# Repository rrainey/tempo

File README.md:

# Tempo

## One Project, Three Boards

This repository is a collection point for a number of jump logging devices I designed for skydivers.

Three boards are part of the Tempo project: Tempo-BT, Tempo, and Peakick. All three explore modern sensor ICs for use in skydiving.  The Peakick board is more research oriented. 
Peakick is design as a daughter board for experimentation with a range of microcontroller boards. It is most easily connected to SparkFun "Thing Plus" form factor boards, although 
it can be connected to almost any modern MCU/SOC board designed for 3.3V peripherals.

Tempo is a purpose built single board logger derived from Peakick.  Essentially, it is a SAMD51 MCU dropped onto a Peakick board.  This project includes PlatformIO-based firmware to drive this board as a stand-alone
skydiving data logger.  The firmware is operational and reliable and I use this board most often for my logging experiments.

### Tempo-BT: Experiments in audible feedback for skydivers.

This project was originally designed to experiment with real-time audible feedback at assist a skydiver in freefall. The original Peakick design stacks a [SparkFun ESP32 Thing Plus](https://github.com/sparkfun/STM32_Thing_Plus) atop a custom GNSS/sensor combo board. The SparkFun board supports an audio connection to Bluetooth earbuds or headphones.  That work led me to design the Tempo-BT board.

### Sensors and Capabilities

- GPS/GNSS using a u-blox SAM-M10Q
- 6-DOF Inertial measurement / gyro using a ICM-42688-V
- Barometric pressure / temperature using a BPM390
- 3-DOF Compass/Magnetic measurement using a MMC5983MA

I am just getting started with this project, so all I'm doing for now is validating the sensor board designs and (soon) experimenting with basic BT audio capabilities.

## Directory Structure

| Folder      | Description |
| ----------- | ----------- |
| hardware    | KiCad PCB projects (using KiCad 7)    |
| hardware/peakick | (original) u-blox GNSS + IMU + Barometric sensor PCB |
| hardware/tempo |(newer design)  SAMD51 + u-blox GNSS + IMU + Barometric sensor PCB |
| hardware/tempo-bt |(newest design) u-blox NORA-B106 Bluetooth SOC (Nordic nRF5340) + u-blox GNSS + IMU + Barometric sensor PCB |
| enclosure    | 3D-printable enclosures (Fusion360 format)
| firmware    | various Arduino sketches (mostly for historical reference)       |
| platformio  | Platformio test and operational projects for the Tempo board |
| platformio/tempo-logger  | Skydiving logger firmware for the Tempo board - tested and reliable |

## Enclosure

The enclosures are designed to be SLA printable. I print using a MakerBot Replicator 2 with Cura 5.3.1 as the slicer. Print resolution set to 0.15mm.

The PCBs are secured to the enclosure using M2.5 brass inserts and screws. The inserts are heat-inserted into the bottom shell using a soldering iron after printing.

### PCB Notes

All three boards were created using KiCad.  In Peakick, in order to get the header alignment with the parent board as accurate as possible, I imported the [SparkFun STM32 Thing Plus](https://github.com/sparkfun/STM32_Thing_Plus) GitHub project to use its PCB layout. 

I prefer 1 oz. Copper with ENIG finish. I ordered the Peakick V1 PCB from OSHPark and stencils from OSH as well.  Tempo boards were ordered from PCBWay.

## Peakick Assembly Parts List

| QTY | MPN      | Description |
|----| ----------- | ----------- |
| 1 | [WRL-15663](https://www.digikey.com/en/products/detail/sparkfun-electronics/WRL-15663/11506265)   | SparkFun ESP32 Thing Plus WROOM
| 1 | N/A   | peakick PCB assembly
| 3  |       | 6 POS 5mm 0.10" receptacle (soldered to peakick PCB)
| 3  |       | 6 POS 0.10" headers
| 1 | [1578](https://www.digikey.com/en/products/detail/adafruit-industries-llc/1578/5054539?utm_adgroup=Battery%20Products&utm_source=google&utm_medium=cpc&utm_campaign=Dynamic%20Search_EN_RLSA_Buyers&utm_term=&utm_content=Battery%20Products&utm_id=go_cmp-175054755_adg-15264279675_ad-399492818526_aud-505192123430:dsa-53357708014_dev-c_ext-_prd-_sig-Cj0KCQjwm66pBhDQARIsALIR2zAggpxuq8dQv4im2FGo1CqTU3N75aE9USMP6jGWoU6Vr5h_xDsHwy8aAp_DEALw_wcB&gclid=Cj0KCQjwm66pBhDQARIsALIR2zAggpxuq8dQv4im2FGo1CqTU3N75aE9USMP6jGWoU6Vr5h_xDsHwy8aAp_DEALw_wcB) | Adafruit 3.7V 500mAH LiPoly rechargeable battery
| 3 | [1GNL7](https://www.grainger.com/product/GRAINGER-APPROVED-Heat-Set-Insert-M2-5-0-45-1GNL7) | Grainger M2.5 Brass Inserts
| 3 |       | M2.5 x 16 mm phillips screws
| 1 | N/A   | Project enclosure (Top and bottom shells)

The two boards are interconnected using 0.1" headers and receptacles. The header/receptacle parts were selected to minimize the gap between the two boards and still allow for quick interchange of each board when required. Nylon spacers are used with each of the mounting screws to minimize the effect of shock and vibration in the electrical interconnections.

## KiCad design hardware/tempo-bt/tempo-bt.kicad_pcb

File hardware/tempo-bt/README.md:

# tempo‑bt V1 board — Peripheral IC Connections 

**Core MCU/Module:** u‑blox NORA‑B106 (nRF5340)
**OS:** Zephyr RTOS
**Goal:** Provide a canonical, test‑ready mapping of logical nets from the NORA‑B106 to each peripheral IC for driver bring‑up and HW connectivity tests.

## High‑level digital interconnect

```mermaid
flowchart LR
  subgraph Core [NORA‑B106 (nRF5340)]
    QSPI[QSPI: SCK, CSN, IO0..IO3]
    SPI4[SPI (SPIM4): SCK, MOSI, MISO, CSN]
    I2C[I²C: SCL, SDA]
    UART_A[UART A: NET_NORA_TX/RX]
    UART_B[UART B: APP_NORA_TX/RX, RTS/CTS]
    VCOM[USB‑UART: VCOM1_TX/RX]
  end

  QSPI --> Flash[MX25R6435F 64Mbit QSPI NOR]
  SPI4 --> IMU[ICM‑42688‑V 6‑axis IMU]
  I2C --> Press[BMP390 Baro]
  I2C --> Mag[MMC5983MA Mag]
  UART_A --> GNSS[SAM‑M10Q GNSS]
  UART_B --> TestApp[App/aux interface]
  VCOM --> HostPC[USB‑UART Console]
```

> Notes
> • Net names and bus roles mirror the labels present on the schematic (e.g., `SPIM4_SCK`, `QSPI_IO0`, `SCL`, `SDA`, `NET_NORA_TX`, `APP_NORA_RTS/CTS`, `VCOM1_RX/TX`).
> • Where interrupts or extra control pins exist but were not explicitly net‑labeled to the MCU on the sheet, they’re called out as **TBD/verify** so you can tag them to specific GPIOs during bring‑up.

---

## User Outputs / Inputs

| Signal | B106 connection | Description |
|--------|----------------|--------------|
| LED1   | `P1.06`          | |
| LED2   | `P0.12`          | |
| BTN1   | `P0.23`          | Pushbutton 1 (with hardware debounce) |
| BTN2   | `P0.24`          | Pushbutton 2 (with hardware debounce) |

## Connectivity tables (by peripheral)

### 1) External QSPI NOR flash — **MX25R6435F (64 Mbit)**

| Bus  | PCB logical net | B106 Port  | Flash pin/function | Notes                                |
| ---- | --------------- | ---------- | ------------------ | ------------------------------------ |
| QSPI | `QSPI_SCK`      | `P0.17/SCK`  | SCLK               | Primary quad SPI clock               |
| QSPI | `QSPI_CSN`      | `P0.18/CSN`  | CS#                | Chip select                          |
| QSPI | `QSPI_IO0`      | `P0.13/IO0`  | IO0 (MOSI/SI)      | Data/IO0                             |
| QSPI | `QSPI_IO1`      | `P0.14/IO1`  | IO1 (MISO/SO)      | Data/IO1                             |
| QSPI | `QSPI_IO2`      | `P0.15/IO2`  | IO2 (WP#)          | Quad IO2 / Write Protect when legacy |
| QSPI | `QSPI_IO3`      | `P0.16/IO3`  | IO3 (HOLD#/RESET#) | Quad IO3 / Hold# when legacy         |

Additional compatibility labels seen on sheet:

* `FLASH_MOSI`, `FLASH_MISO`, `FLASH_SCK` appear alongside the `QSPI_*` set; treat as alternative/legacy SPI naming used at fan‑out or test points.

**Zephyr tips:** Use `jedec,spi-nor` with `qspi` child and 4‑line mode; map `io0..io3` and `cs-gpios` to the same nets as above.

---

### 2) 6‑axis IMU — **ICM‑42688‑V**

| Bus         | PCB net         | B106 Port    | IMU pin/function | Notes                                          |
|:-----------:| --------------- | ----------   |:----------------:| ---------------------------------------------- |
| SPI (SPIM4) | `SPIM4_SCK`     | `P0.08/SCK`  | SCLK             | IMU serial clock                               |
| SPI (SPIM4) | `SPIM4_MOSI`    | `P0.09/MOSI` | SDI              | Master‑out / IMU SDI                           |
| SPI (SPIM4) | `SPIM4_MISO`    | `P0.10/MISO` | SDO              | Master‑in / IMU SDO                            |
| SPI (SPIM4) | `SPIM4_CSN`     | `P0.11/CSN`  | CSB              | Chip select, active low                        |
| GPIO        | **D6**          | `P1.07`      | INT1             | Interrupt to NORA GPIO  |
|   | NC   | NC  | INT2/FSYNC/CLKIN | Optional secondary INT/FSYNC (unconnected)          |

**What’s explicit vs. to‑confirm:** The `SPIM4_*` nets are explicit on the sheet and should route to the IMU serial pins. Interrupt lines are present on the symbol but aren’t labeled to a specific net name at the MCU in the text export I parsed—please tag to the intended GPIOs during DTS authoring.

---

### 3) Barometric pressure — **BMP390**

| Bus        | PCB net | B106 port | BMP390 pin/function | Notes                                 |
|:----------:| ---------------|:------:|:-------------------:| ------------------------------------- |
| I²C        | `SCL` | `P1.02/TWI`        | SCL                 | I²C clock                             |
| I²C        | `SDA` | `P1.03/TWI`        | SDA                 | I²C data                              |
| GPIO | **D11** | `P1.11`     | INT                 | |

---

### 4) Magnetometer — **MMC5983MA**

| Bus        | PCB net | B106 port | MMC5983MA pin/function | Notes                                   |
|:----------:| ----------------|:-----:|:----------------------:| --------------------------------------- |
| I²C        | `SCL`  | `P1.02/TWI`               | SCL                    | Shared I²C clock                        |
| I²C        | `SDA`  | `P1.03/TWI`               | SDA                    | Shared I²C data                         |
| GPIO | **D9**  | `P1.09`      | INT                   |   |

---

### 5) GNSS module — **u‑blox SAM‑M10Q**

Note: V1 board has GNSS UART connections only.  V2 board will connect PPS TIMEPULSE to a GPIO line (line to-be-determined).

| Interface          | NORA‑B106 logical net                | SAM‑M10Q function | Notes                                                                                                                                            |
| ------------------ | ------------------------------------ |:-----------------:| ------------------------------------------------------------------------------------------------------------------------------------------------ |
| UART               | `NET_NORA_TX` → GNSS RX              | RXD               | Primary GNSS serial in                                                                                                                           |
| UART               | `NET_NORA_RX` ← GNSS TX              | TXD               | Primary GNSS serial out                                                                                                                          |
| UART (alt/app)     | `APP_NORA_TX/RX`, `APP_NORA_RTS/CTS` | TX/RX/RTS/CTS     | A second NORA UART is brought out as “APP\_NORA\_\*”; use if the GNSS is wired to the app port or for auxiliary host/debug depending on stuffing |
| USB‑UART (console) | `VCOM1_TX/RX`                        | TX/RX             | Labeled console link to host PC/bridge; useful for test logging                                                                                  |

> The schematic contains `NET_NORA_TX/RX` and also `APP_NORA_*` plus `VCOM1_*`. Use the pair that terminates on the SAM‑M10Q in your assembled option. For Zephyr, declare the chosen UART instance as `gps0` with `ubx,m10` (or use NMEA‑compatible driver) and disable the unused one(s).

---

## Zephyr bring‑up checklist (how to use this map)

1. **Pick instances**

   * QSPI: enable nRF QSPI controller, bind `cs-gpios` and `io0..io3` to `QSPI_*`.
   * SPI: enable `spi4` (SPIM4) and bind to IMU.
   * I²C: enable the I²C controller feeding `SCL/SDA` bus; add BMP390 + MMC5983MA as children with proper addresses.
   * UART: choose **either** `NET_NORA_*` (GNSS) **or** `APP_NORA_*` based on your assembly; reserve `VCOM1_*` for console.

2. **GPIOs/interrupts**

   * Assign IMU `INT1` and the magnetometer `INT` to listed GPIOs
   * Add `interrupts = <&gpioX pin IRQ_EDGE_RISING>;` in each child node.

3. **Testing hooks**

   * Flash: probe with JEDEC ID over QSPI, read SFDP.
   * IMU: WHO\_AM\_I on `SPIM4`; read INT on motion.
   * Baro/Mag: ID registers over I²C; poll data‑ready.
   * GNSS: open UART, request UBX‑MON‑VER, check NMEA stream.
   * Console: ensure `VCOM1_*` maps to the chosen Zephyr `console`.

---

## Appendix — Signal name index (as found on the sheet)

From the schematic net labels (selection):
`QSPI_SCK`, `QSPI_CSN`, `QSPI_IO0`, `QSPI_IO1`, `QSPI_IO2`, `QSPI_IO3`, `FLASH_MOSI`, `FLASH_MISO`, `FLASH_SCK`, `SPIM4_SCK`, `SPIM4_MOSI`, `SPIM4_MISO`, `SPIM4_CSN`, `SCL`, `SDA`, `NET_NORA_TX`, `NET_NORA_RX`, `APP_NORA_TX`, `APP_NORA_RX`, `APP_NORA_RTS`, `APP_NORA_CTS`, `VCOM1_TX`, `VCOM1_RX`, `SWDIO`, `SWDCLK`, `~RESET`, `BTN1`, `BTN2`, `BTN3`, `BTN4`, `D5`, `D6`, `D7`, `D9`, `D10`, `D11`, `D12`, `D13`, `P0.31`, `XL1`, `XL2`, `VDDIO`, `VBACKUP`.

`D*` lines (`D5` .. `D13`) were selected to correspond the the nRF8340 Arduino developement kit board definition.

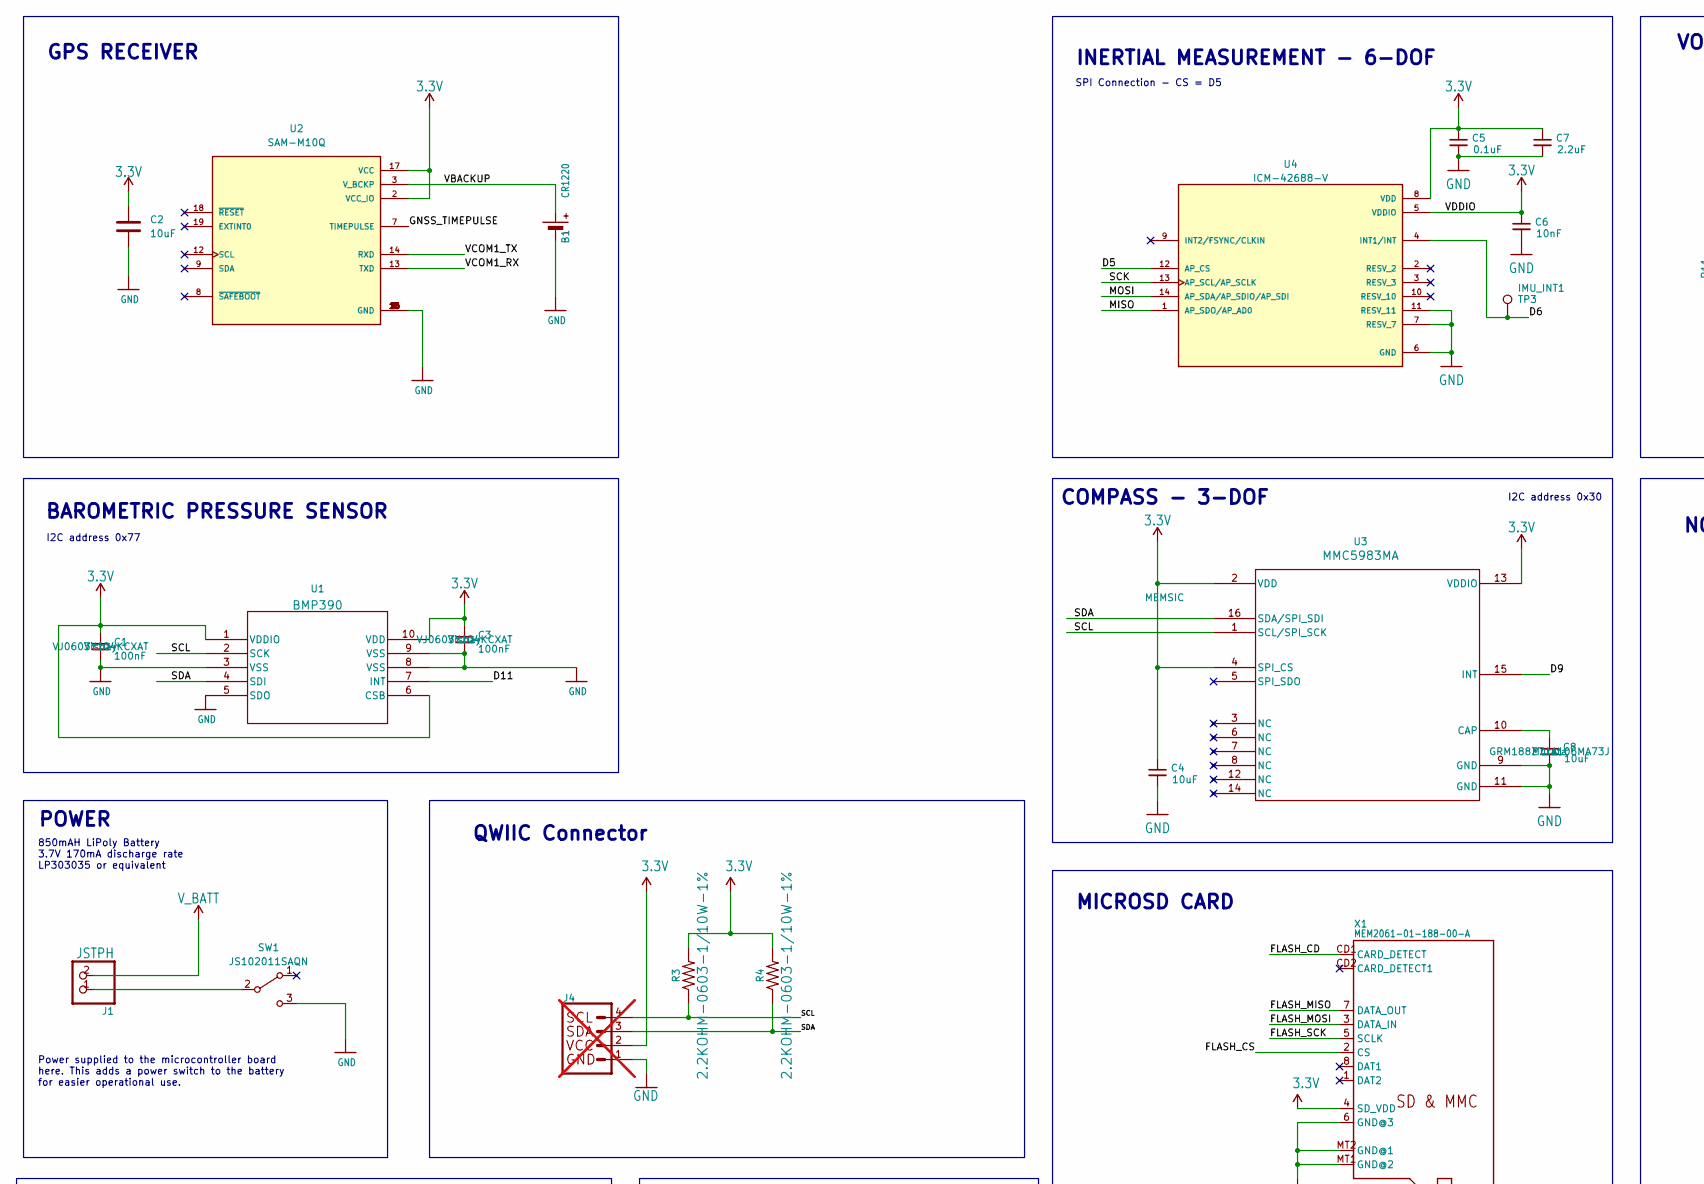
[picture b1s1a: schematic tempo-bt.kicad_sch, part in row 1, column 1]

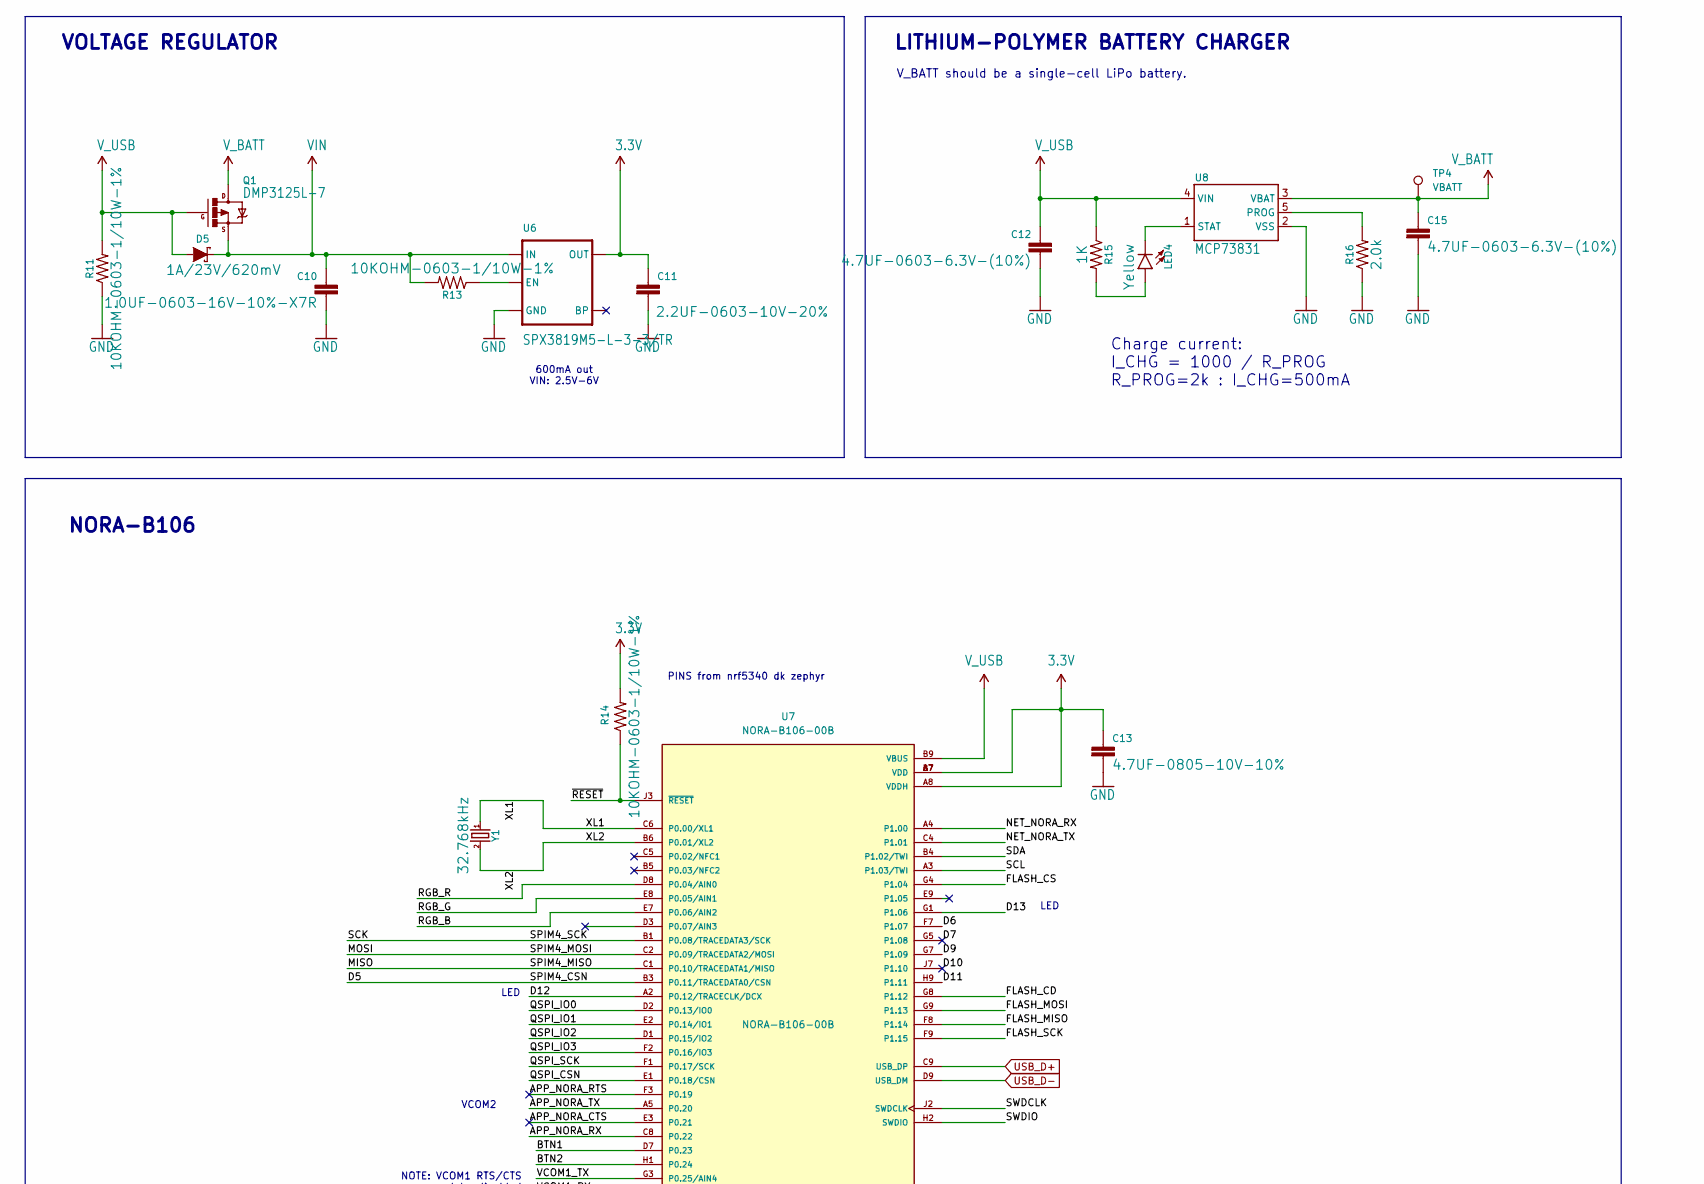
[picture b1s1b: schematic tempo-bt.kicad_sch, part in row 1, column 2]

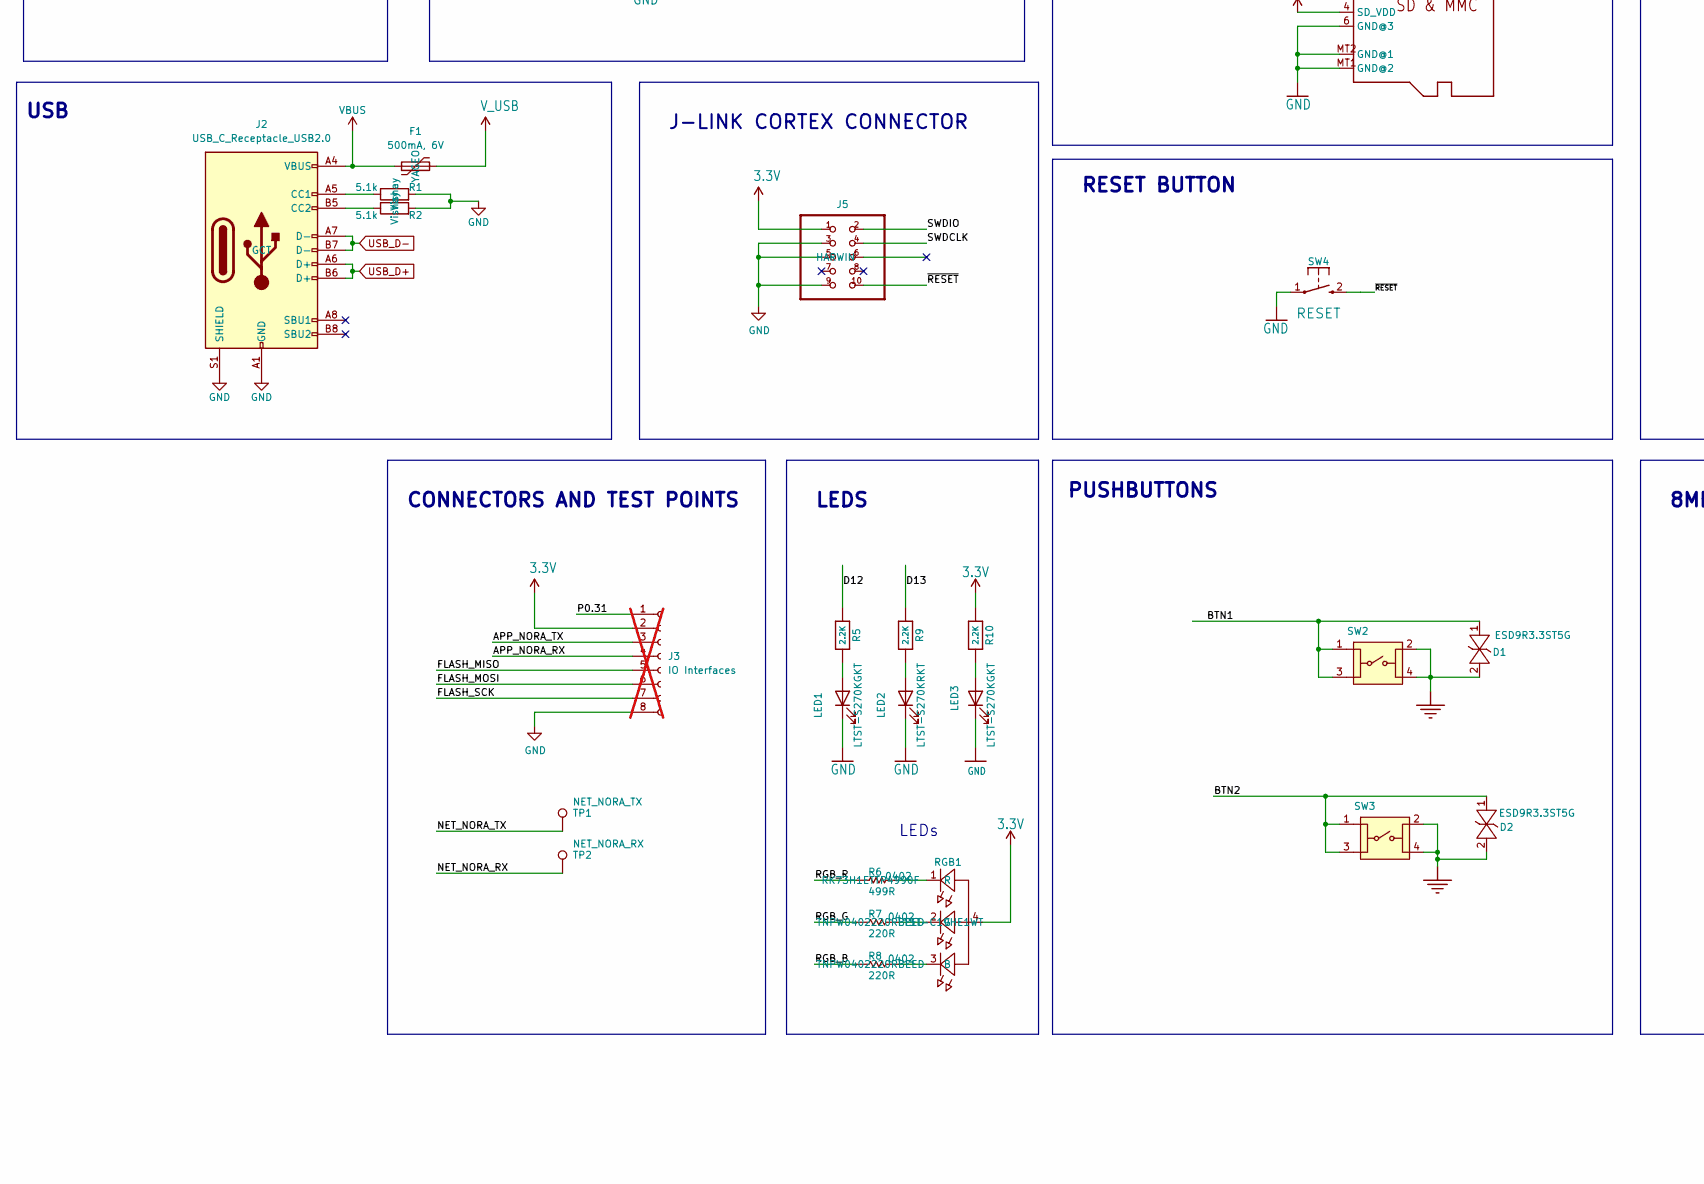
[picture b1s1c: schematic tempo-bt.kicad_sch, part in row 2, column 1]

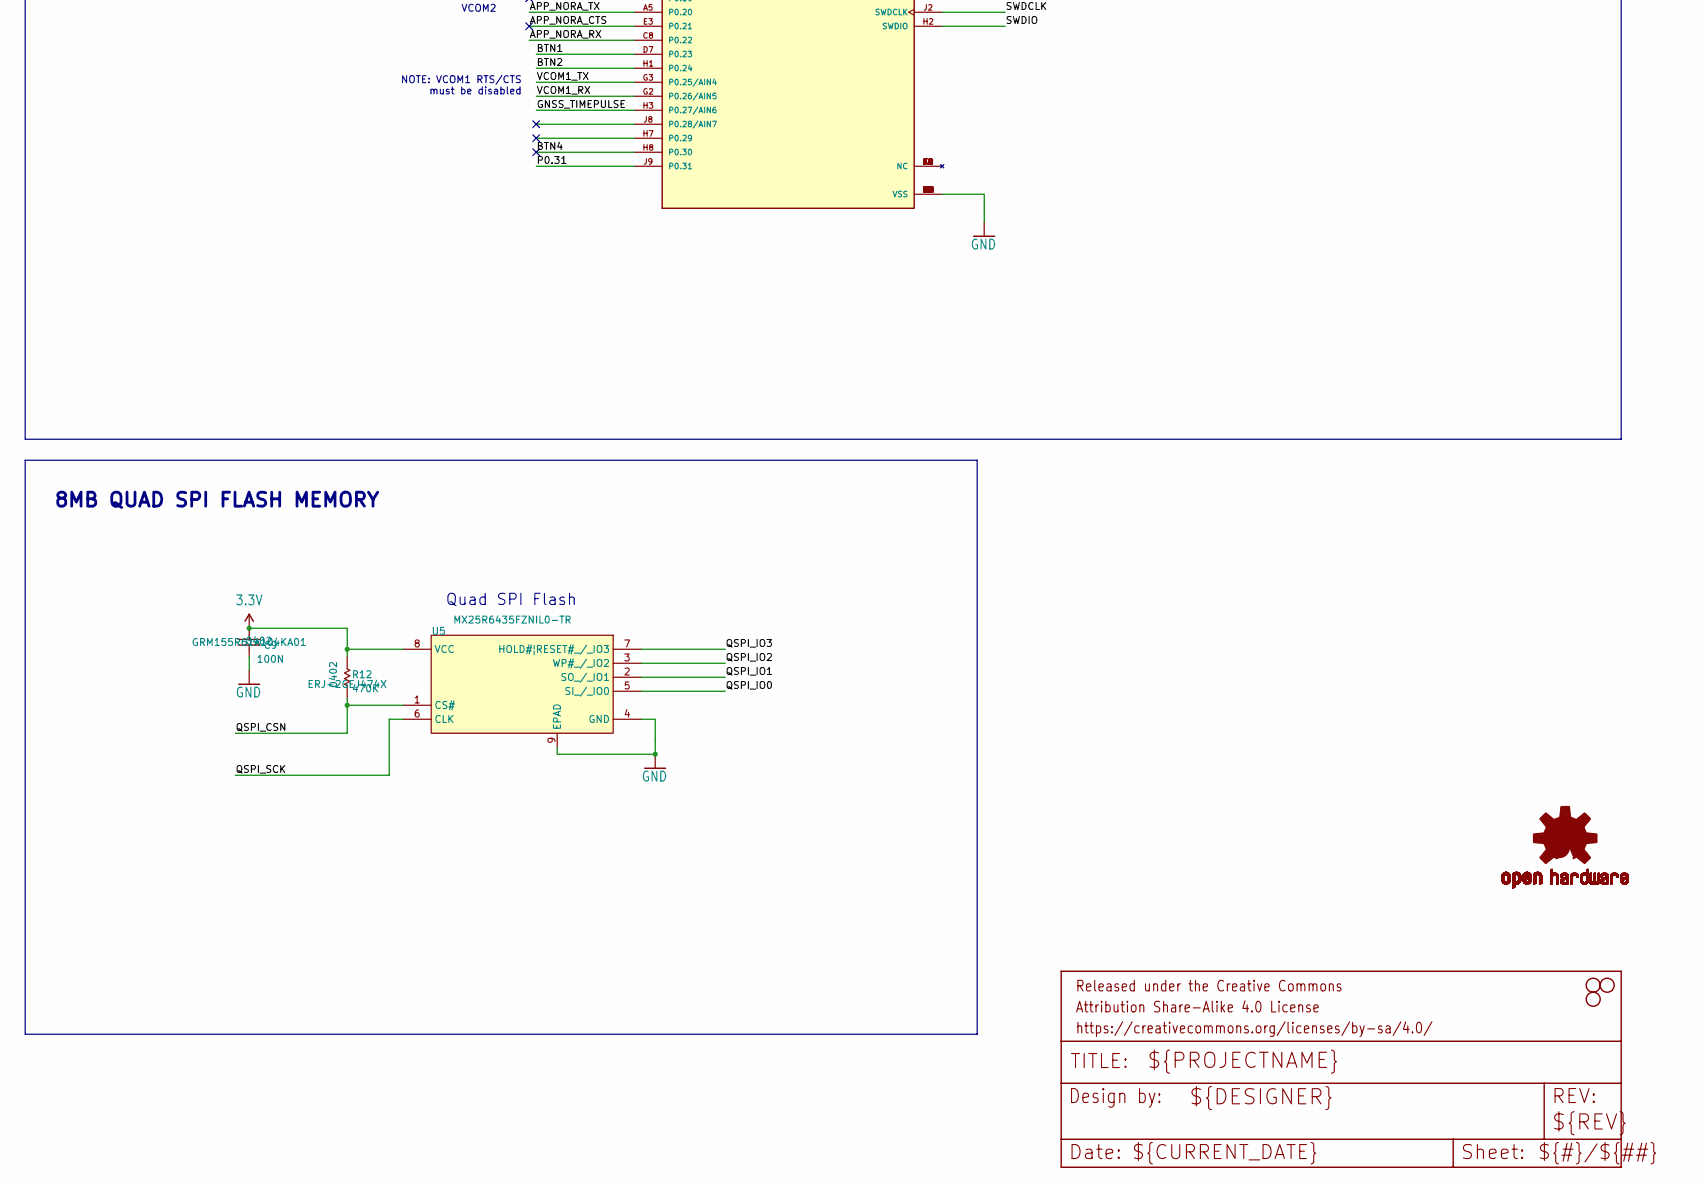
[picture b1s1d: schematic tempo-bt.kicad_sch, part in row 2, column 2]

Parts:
B1: CR1220; CR1220-2; MPN 1056TR
C1, C3: 100nF; C_0603_1608Metric; MPN VJ0603Y104KCXAT
C2, C4, C8: 10uF; C_0603_1608Metric; MPN GRM188Z71A106MA73J
C5: 0.1uF; C_0603_1608Metric; MPN GRT033C81A104KE01D
C6: 10nF; C_0603_1608Metric; MPN CGA3E2X7R1H103K080AE
C7: 2.2uF; C_0603_1608Metric; MPN GRM188R71A225KE15D
C9: 100nF; C_0402_1005Metric; TOLERANCE 10%; MAX VOLTAGE 10V; PART NUMBER UBXH01-2021002
C10: 1.0UF-0603-16V-10%-X7R; C_0603_1608Metric; MPN 0603DC105KAT2A
C11: 2.2UF-0603-10V-20%; C_0603_1608Metric; MPN GRM188Z71C225KE43D
C12, C15: 4.7UF-0603-6.3V-(10%); C_0603_1608Metric; MPN GRM188Z71A475KE15D
C13: 4.7UF-0805-10V-10%; 0805; MPN GRM21BR71A475KE51L
D1, D2: UBXH07-0000034${DNP}; D_SOD-923; PART NUMBER UBXH07-0000034
D5: 1A/23V/620mV; SOD-323; MPN BAT20JFILM
F1: 500mA, 6V; Fuse_0805_2012Metric; MPN SMD0805B050TF; JLCPCB Part # C269104
FRAME1: FRAME-LETTER; CREATIVE_COMMONS
H1, H2, H3: STAND-OFFTIGHT; STAND-OFF-TIGHT
J1: JSTPH; JSTPH2; Manufacturer Part S2B-PH-SM4-TB
J2: USB_C_Receptacle_USB2.0; GCT-USB4105-GF-A modified-USB-C 16P; MPN USB4105-GF-A-120; JLCPCB Part # C168688
J3: IO Interfaces; PinHeader_1x08_P1.27mm_Vertical; not fitted
J4: QWIIC_CONNECTORJS-1MM; JST04_1MM_RA; MPN SM04B-SRSS-TB; not fitted
J5: 2x5 PTH ARM CORTEX DEBUG; 2X5-PTH-1.27MM-NO_SILK; MPN M50-3500542
LED1, LED3: LTST-S270KGKT; LED_0603_1608Metric; MPN LTST-S270KGKT
LED2: LTST-S270KRKT; LED_0603_1608Metric; MPN LTST-S270KRKT
LED4: Yellow; LED-0603; MPN LTST-S270YKT
LOGO1: OSHW-LOGOS; OSHW-LOGO-S
Q1: DMP3125L-7; SOT23-3@1; MPN DMP3125L-7
R1, R2: 5.1k; R_0402_1005Metric; MPN RCC04025K10FKED; JLCPCB Part # C25905
R3, R4: 2.2KOHM-0603-1/10W-1%; 0603; MPN ERJ-H3EF2201V
R5, R9, R10: 2.2K; R_0603_1608Metric; MPN ERJ-H3EF2201V
R6: 499OHM-0402; R_0402_1005Metric; TOLERANCE 1%; PART NUMBER UBXH18-0000269
R7, R8: 220OHM-0402; R_0402_1005Metric; TOLERANCE 5%; PART NUMBER UBXH18-0008033
R11, R13, R14: 10KOHM-0603-1/10W-1%; 0603; MPN ERJ-H3EF1002V
R12: 470KOHM; R_0402_1005Metric; TOLERANCE 5%; PART NUMBER UBXH18-0008113
R15: 1K; 0603; MPN MR06X1001FTL
R16: 2.0k; 0603; MPN MR06X2001FTL
RGB1: LTST-C19HE1WT; MAX VOLTAGE 5V; PART NUMBER UBXH11-0000058
SW1: JS102011SAQN; MPN JS102011SAQN
SW2, SW3: PTS850; PTS850-with-bosses; PART NUMBER UBXH19-0000035
SW4: RESET; SW_Push_1P1T_NO_CK_KMR2; MPN KMR221NG LFS
TP1: NET_NORA_TX; TestPoint_Pad_1.0x1.0mm
TP2: NET_NORA_RX; TestPoint_Pad_1.0x1.0mm
TP3: IMU_INT1; TestPoint_THTPad_1.0x1.0mm_Drill0.5mm
TP4: VBATT; TestPoint_THTPad_1.0x1.0mm_Drill0.5mm
U1: BMP390; LGA10_BMP390_BOS; MPN BMP390
U2: SAM-M10Q; MODULE_SAM-M8Q-0-10; PARTREV R07
U3: MMC5983MA; MMC5983MA_MEM; MPN MMC5983MA
U4: ICM-42688-V; PQFN50P300X250X97-14N; PARTREV 1.2
U5: MX25R64; WSON-8-1EP_6x5mm_P1.27mm_EP3.4x4mm; PART NUMBER UBXH13-0000138
U6: SPX3819M5-L-3-3/TR; SOT23-5; MPN SPX3819M5-L-3-3/TR
U7: NORA-B106-00B; XCVR_NORA-B106-00B; PARTREV R05
U8: MCP73831; SOT23-5; MPN MCP73831T-4ADI/OT
X1: MEM2061-01-188-00-A; MICROSD; MPN MEM2061-01-188-00-A
Y1: 32.768kHz; CRYSTAL-SMD-3.2X1.5MM; MPN ABS07-120-32.768KHZ-T

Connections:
3.3V: C1.1, C2.1, C3.1, C4.1, C5.1, C6.1, C7.1, C9.1, C11.1, C13.1, J3.2, J4.2, J5.1, R3.2, R4.2, R10.1, R12.2, R14.2, RGB1.4 (A), U1.1 (VDDIO), U1.6 (CSB), U1.10 (VDD), U2.2 (VCC_IO), U2.17 (VCC), U3.2 (VDD), U3.4 (SPI_CS), U3.13 (VDDIO), U4.5 (VDDIO), U4.8 (VDD), U5.8 (VCC), U6.5 (OUT), U7.A7 (VDD), U7.A8 (VDDH), U7.B7 (VDD), X1.4 (SD_VDD)
/APP_NORA_CTS: U7.E3 (P0.21)
/APP_NORA_RTS: U7.F3 (P0.19)
/APP_NORA_RX: J3.4, U7.C8 (P0.22)
/APP_NORA_TX: J3.3, U7.A5 (P0.20)
/BTN1: D1.1, SW2.1, SW2.3, U7.D7 (P0.23)
/BTN2: D2.1, SW3.1, SW3.3, U7.H1 (P0.24)
/BTN4: U7.H8 (P0.30)
/D5: U4.12 (AP_CS), U7.B3 (P0.11/TRACEDATA0/CSN)
/D6: TP3.1, U4.4 (INT1/INT), U7.F7 (P1.07)
/D7: U7.G5 (P1.08)
/D9: U3.15 (INT), U7.G7 (P1.09)
/D10: U7.J7 (P1.10)
/D11: U1.7 (INT), U7.H9 (P1.11)
/D12: R5.1, U7.A2 (P0.12/TRACECLK/DCX)
/D13: R9.1, U7.G1 (P1.06)
/FLASH_CD: U7.G8 (P1.12), X1.CD1 (CARD_DETECT)
/FLASH_CS: U7.G4 (P1.04), X1.2 (CS)
/FLASH_MISO: J3.5, U7.F8 (P1.14), X1.7 (DATA_OUT)
/FLASH_MOSI: J3.6, U7.G9 (P1.13), X1.3 (DATA_IN)
/FLASH_SCK: J3.7, U7.F9 (P1.15), X1.5 (SCLK)
/GNSS_TIMEPULSE: U2.7 (TIMEPULSE), U7.H3 (P0.27/AIN6)
/MISO: U4.1 (AP_SDO/AP_AD0), U7.C1 (P0.10/TRACEDATA1/MISO)
/MOSI: U4.14 (AP_SDA/AP_SDIO/AP_SDI), U7.C2 (P0.09/TRACEDATA2/MOSI)
/NET_NORA_RX: TP2.1, U7.A4 (P1.00)
/NET_NORA_TX: TP1.1, U7.C4 (P1.01)
/P0.31: J3.1, U7.J9 (P0.31)
/QSPI_CSN: R12.1, U5.1 (CS#), U7.E1 (P0.18/CSN)
/QSPI_IO0: U5.5 (SI_/_IO0), U7.D2 (P0.13/IO0)
/QSPI_IO1: U5.2 (SO_/_IO1), U7.E2 (P0.14/IO1)
/QSPI_IO2: U5.3 (WP#_/_IO2), U7.D1 (P0.15/IO2)
/QSPI_IO3: U5.7 (HOLD#¦RESET#_/_IO3), U7.F2 (P0.16/IO3)
/QSPI_SCK: U5.6 (CLK), U7.F1 (P0.17/SCK)
/RGB_B: R8.1, U7.E7 (P0.06/AIN2)
/RGB_G: R7.1, U7.E8 (P0.05/AIN1)
/RGB_R: R6.1, U7.D8 (P0.04/AIN0)
/SCK: U4.13 (AP_SCL/AP_SCLK), U7.B1 (P0.08/TRACEDATA3/SCK)
/SCL: J4.4, R3.1, U1.2 (SCK), U3.1 (SCL/SPI_SCK), U7.A3 (P1.03/TWI)
/SDA: J4.3, R4.1, U1.4 (SDI), U3.16 (SDA/SPI_SDI), U7.B4 (P1.02/TWI)
/SWDCLK: J5.4, U7.J2 (SWDCLK)
/SWDIO: J5.2, U7.H2 (SWDIO)
/VBACKUP: B1.+, U2.3 (V_BCKP)
/VCOM1_RX: U2.13 (TXD), U7.G2 (P0.26/AIN5)
/VCOM1_TX: U2.14 (RXD), U7.G3 (P0.25/AIN4)
/XL1: U7.C6 (P0.00/XL1), Y1.P$1 (1)
/XL2: U7.B6 (P0.01/XL2), Y1.P$2 (2)
/~RESET: J5.10, R14.1, SW4.2, U7.J3 (~RESET)
GND: B1.-, C1.2, C2.2, C3.2, C4.2, C5.2, C6.2, C7.2, C8.2, C9.2, C10.2, C11.2, C12.2, C13.2, C15.2, D1.2, D2.2, J2.A1 (GND), J2.A12 (GND), J2.B1 (GND), J2.B12 (GND), J2.S1 (SHIELD), J3.8, J4.1, J5.3, J5.5, J5.9, LED1.1 (K), LED2.1 (K), LED3.1 (K), R1.2, R2.2, R11.1, R16.1, SW1.3 (C), SW2.2, SW2.4, SW3.2, SW3.4, SW4.1, U1.3 (VSS), U1.5 (SDO), U1.8 (VSS), U1.9 (VSS), U2.1 (GND), U2.4 (GND), U2.5 (GND), U2.6 (GND), U2.10 (GND), U2.11 (GND), U2.15 (GND), U2.16 (GND), U2.20 (GND), U3.9 (GND), U3.11 (GND), U4.6 (GND), U4.7 (RESV_7), U4.11 (RESV_11), U5.4 (GND), U5.9 (EPAD), U6.2 (GND), U7.A1 (VSS), U7.A9 (VSS), U7.B2 (VSS), U7.B8 (VSS), U7.E4 (VSS), U7.E5 (VSS), U7.F4 (VSS), U7.F5 (VSS), U7.K2 (VSS), U7.K3 (VSS), U7.K5 (VSS), U7.K7 (VSS), U7.K8 (VSS), U7.L1 (VSS), U7.L9 (VSS), U7.M1 (VSS), U7.M2 (VSS), U7.M8 (VSS), U7.M9 (VSS), U8.2 (VSS), X1.6 (GND@3), X1.MT1 (GND@2), X1.MT2 (GND@1)
unnamed: J2.A5 (CC1), R1.1
unnamed: J2.B5 (CC2), R2.1
unnamed: LED1.2 (A), R5.2
unnamed: LED2.2 (A), R9.2
unnamed: LED3.2 (A), R10.2
unnamed: LED4.A, R15.2
unnamed: R8.2, RGB1.3 (B)
unnamed: R7.2, RGB1.2 (G)
unnamed: R6.2, RGB1.1 (R)
unnamed: J1.1, SW1.2 (B)
unnamed: C8.1, U3.10 (CAP)
unnamed: R13.1, U6.3 (EN)
unnamed: R16.2, U8.5 (PROG)
unnamed: LED4.C, U8.1 (STAT)
USB_D+: J2.A6 (D+), J2.B6 (D+), U7.C9 (USB_DP)
USB_D-: J2.A7 (D-), J2.B7 (D-), U7.D9 (USB_DM)
VBUS: F1.1, J2.A4 (VBUS), J2.A9 (VBUS), J2.B4 (VBUS), J2.B9 (VBUS)
VIN: C10.1, D5.C, Q1.2 (S), R13.2, U6.1 (IN)
V_BATT: C15.1, J1.2, Q1.3 (D), TP4.1, U8.3 (VBAT)
V_USB: C12.1, D5.A, F1.2, Q1.1 (G), R11.2, R15.1, U7.B9 (VBUS), U8.4 (VIN)

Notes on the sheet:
600mA out VIN: 2.5V-6V
GPS RECEIVER
SPI Connection - CS = D5
COMPASS - 3-DOF
BAROMETRIC PRESSURE SENSOR
J-LINK CORTEX CONNECTOR
POWER
V_BATT should be a single-cell LiPo battery.
VOLTAGE REGULATOR
Charge current: I_CHG = 1000 / R_PROG R_PROG=2k : I_CHG=500mA
LED
INERTIAL MEASUREMENT - 6-DOF
LEDs
CONNECTORS AND TEST POINTS
850mAH LiPoly Battery 3.7V 170mA discharge rate LP303035 or equivalent
Power supplied to the microcontroller board here. This adds a power switch to the battery for easier operational use.
PUSHBUTTONS
QWIIC Connector
MICROSD CARD
LITHIUM-POLYMER BATTERY CHARGER
RESET BUTTON
Quad SPI Flash
VCOM2
NOTE: VCOM1 RTS/CTS must be disabled
USB
I2C address 0x77
I2C address 0x30
8MB QUAD SPI FLASH MEMORY
NORA-B106
PINS from nrf5340 dk zephyr
LEDS

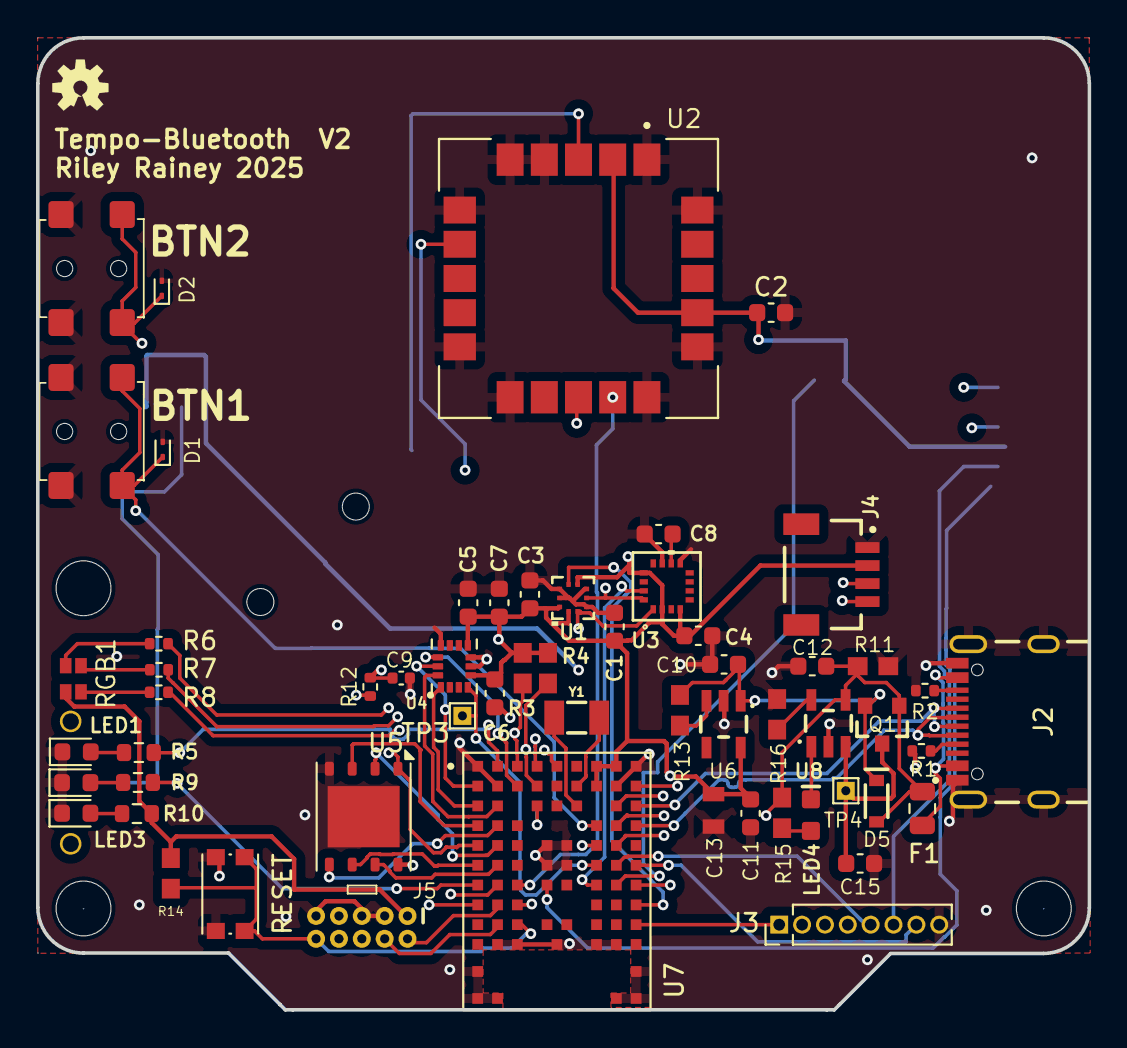
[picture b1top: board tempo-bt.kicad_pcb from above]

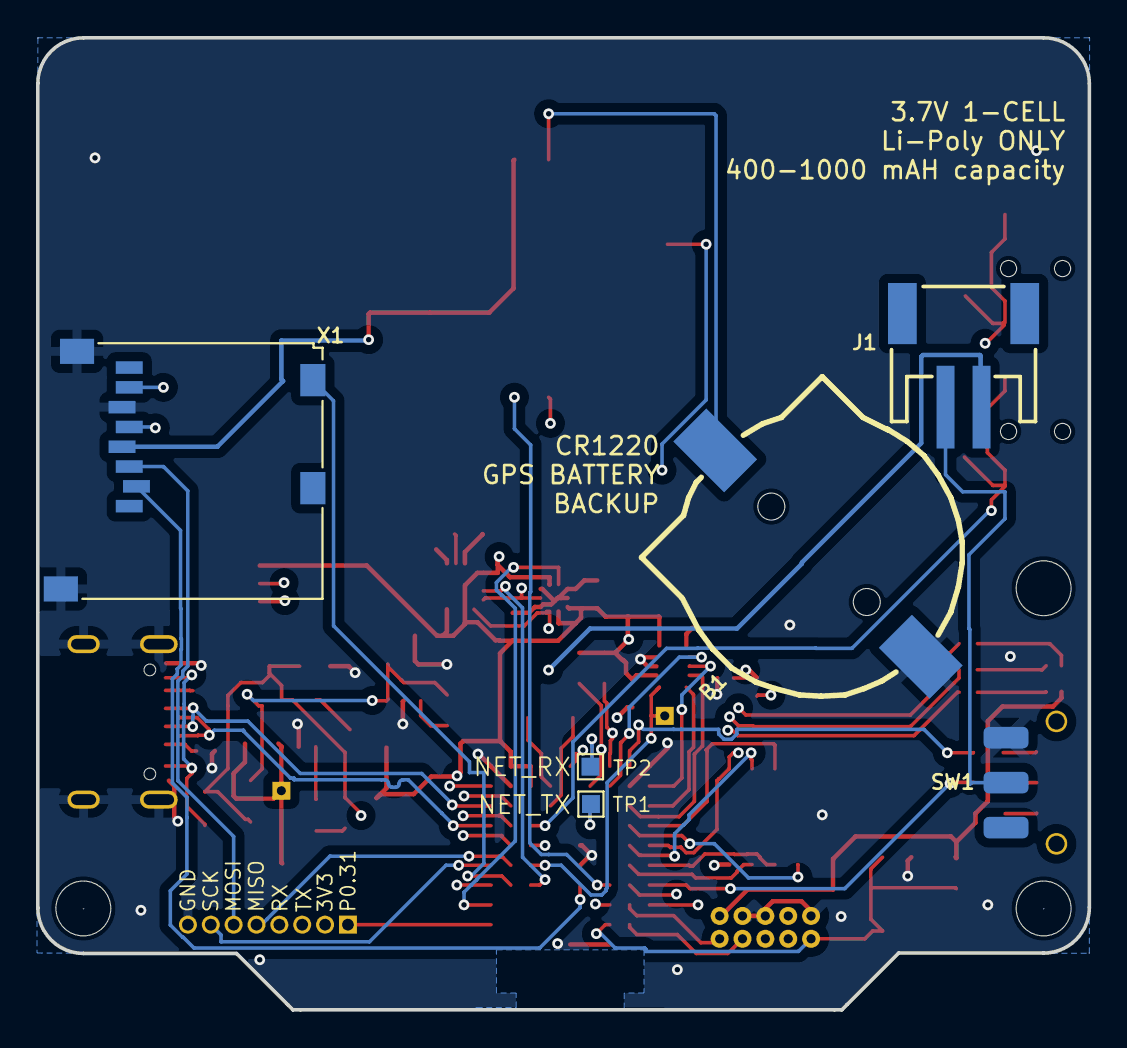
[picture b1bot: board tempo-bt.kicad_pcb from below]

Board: 4 copper layers, 58.4 x 54.0 mm, 69 parts (6 on the bottom side), 63 nets.

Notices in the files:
hardware/tempo-bt/tempo-bt.kicad_sch:
Released under the Creative Commons
https://creativecommons.org/licenses/by-sa/4.0
parts and their libraries:
Released under the Creative Commons Attribution Share-Alike 4.0 License
